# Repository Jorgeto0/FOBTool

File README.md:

# FOBtool Hardware

FOBtool Hardware is the KiCad source repository for the FOBtool handheld electronic platform. It contains the project-level schematic and PCB files, custom symbols and footprints, and supporting documentation used to develop and maintain the hardware design.

## Project contents

| Path | Purpose |
| --- | --- |
| `FOBtool_HW.kicad_pro` | Main KiCad project file. Open this file to work with the design. |
| `FOBtool_HW.kicad_sch` | Top-level hierarchical schematic. |
| `POWER.kicad_sch` | Battery, charging, power-path, monitoring, and regulated-supply circuitry. |
| `MAIN_CONTROLLER_sch.kicad_sch` | ESP32-S3 main-controller circuitry and system control interfaces. |
| `FOBtool_HW.kicad_pcb` | PCB layout file. |
| `Custom_Components/` | Project-specific symbol and footprint resources. |
| `docs/` | Short descriptions of the project and schematic sheets. |

## Opening the design

1. Install [KiCad](https://www.kicad.org/) 10.x or a compatible later version.
2. Clone or download the complete repository so the project files and custom libraries remain together.
3. Open `FOBtool_HW.kicad_pro` from KiCad's Project Manager.
4. Confirm that the project symbol and footprint libraries load without errors before editing the design.

Open the project file rather than an individual child sheet so KiCad retains the full hierarchy and project library configuration.

## Schematic documentation

See the [documentation index](docs/README.md) for the purpose of each schematic sheet currently included in the project.

## Repository use

This repository contains active engineering source files. Design files may change as schematic capture, verification, PCB layout, and manufacturing preparation progress. Manufacturing outputs should be issued separately as a controlled release.

## Confidentiality

This project contains proprietary client hardware information. Keep the repository private and share its contents only with authorized project participants.

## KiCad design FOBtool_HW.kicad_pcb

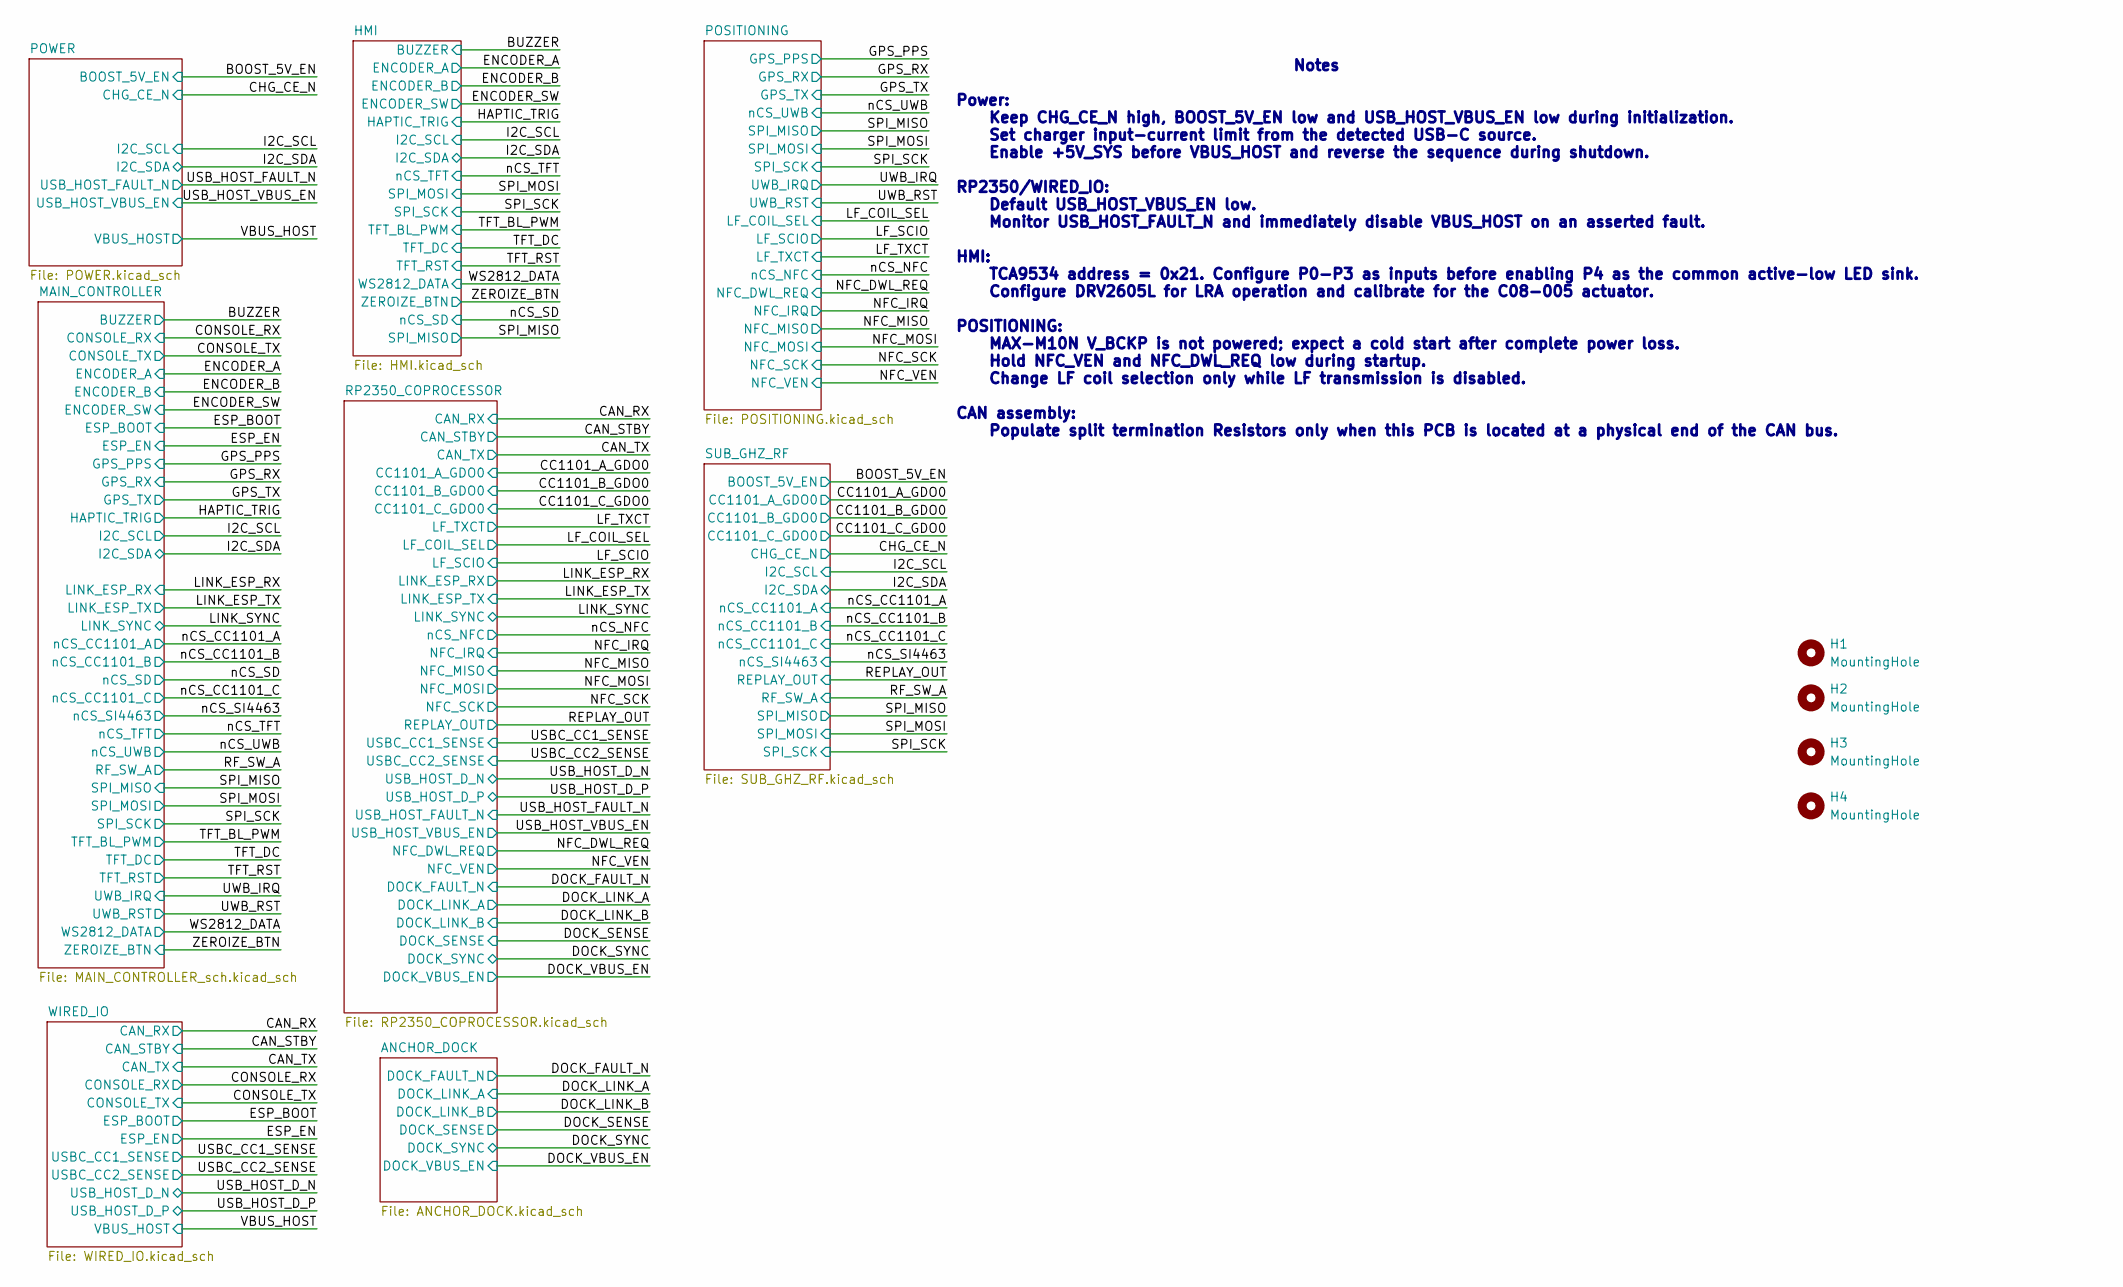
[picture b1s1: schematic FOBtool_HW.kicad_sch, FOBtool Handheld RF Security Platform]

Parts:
H1, H2, H3, H4: MountingHole; MountingHole_2.2mm_M2

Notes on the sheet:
Notes Power: Keep CHG_CE_N high, BOOST_5V_EN low and USB_HOST_VBUS_EN low during initialization. Set charger input-current limit from the detected USB-C source. Enable +5V_SYS before VBUS_HOST and reverse the sequence during shutdown. RP2350/WIRED_IO: Default USB_HOST_VBUS_EN low. Monitor USB_HOST_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

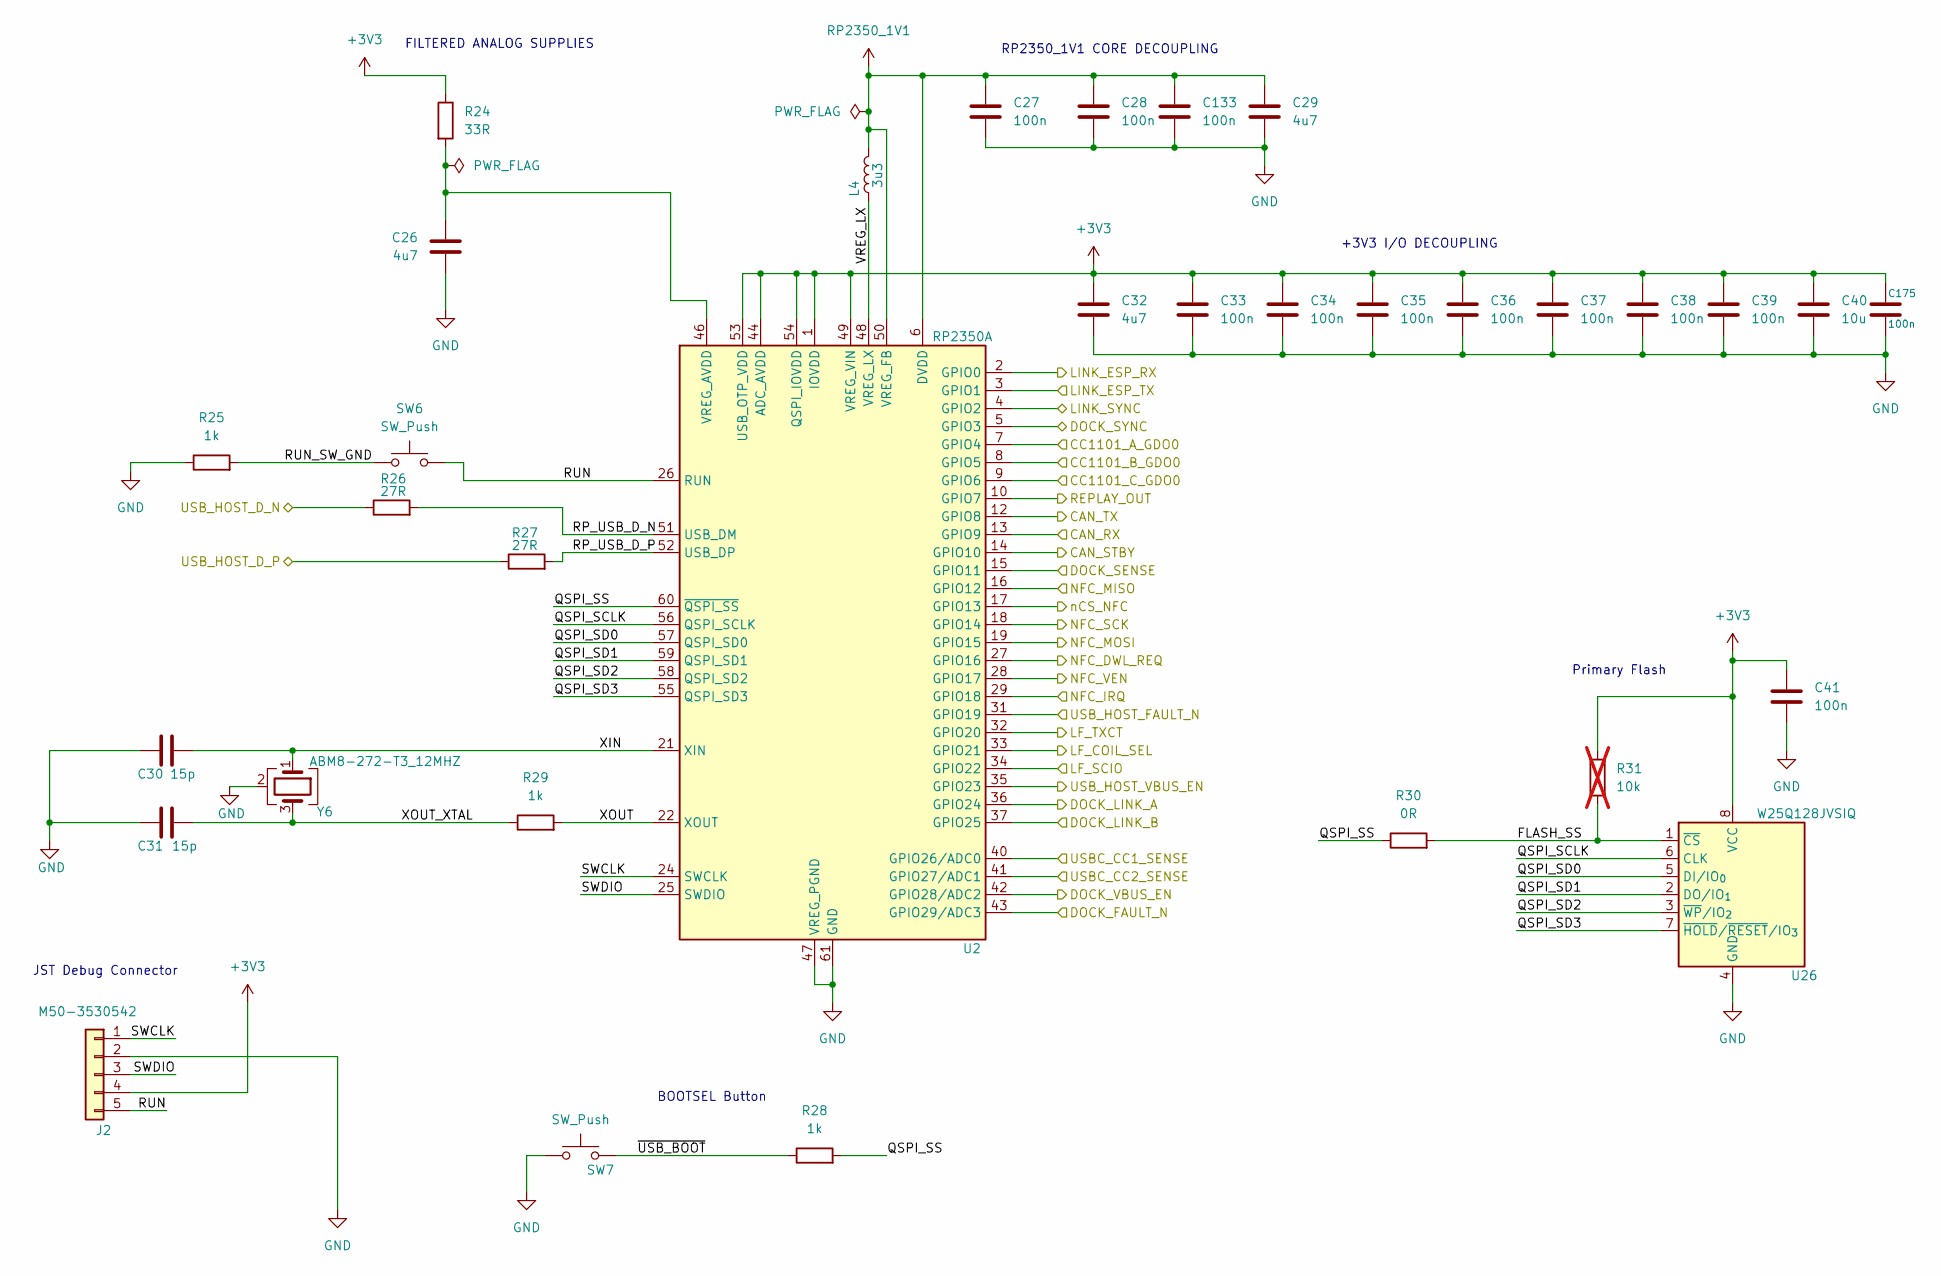
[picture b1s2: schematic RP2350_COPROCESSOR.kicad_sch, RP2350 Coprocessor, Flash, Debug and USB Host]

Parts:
C26, C29, C32: 4u7; C_0603_1608Metric; MPN GRM188Z71A475KE15D
C27, C28, C33, C34, C35, C36, C37, C38, C39, C41, C133, C175: 100n; C_0402_1005Metric; MPN GRM155R71C104KA88D
C30, C31: 15p; C_0402_1005Metric; MPN GJM1555C1H150JB01D
C40: 10u; C_0805_2012Metric; MPN GRM21BR71A106KE51L
J2: M50-3530542; PinHeader_1x05_P1.27mm_Vertical; MPN M50-3530542
L4: 3u3; L_Abracon_AOTA-B201610S_2.0x1.6mm; MPN AOTA-B201610S3R3-101-T
R24: 33R; R_0603_1608Metric; MPN RC0603FR-0733RL
R25, R28, R29: 1k; R_0603_1608Metric; MPN RC0603FR-071KL
R26, R27: 27R; R_0603_1608Metric; MPN RC0603FR-0727RL
R30: 0R; R_0603_1608Metric; MPN RC0603JR-070RL
R31: 10k; R_0603_1608Metric; MPN RC0603FR-0710KL; not fitted
SW6, SW7: SW_Push; SW_SPST_PTS810; MPN PTS810SJM250SMTR LFS
U2: RP2350A; QFN-60-1EP_7x7mm_P0.4mm_EP3.4x3.4mm; MPN SC1509(13)-A4
U26: W25Q128JVSIQ; SOIC-8_5.3x5.3mm_P1.27mm; MPN W25Q128JVSIQTR
Y6: ABM8-272-T3_12MHZ; Crystal_SMD_Abracon_ABM8G-4Pin_3.2x2.5mm; MPN ABM8-272-T3

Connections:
+3V3: C32.1, C33.1, C34.1, C35.1, C36.1, C37.1, C38.1, C39.1, C40.1, C41.1, C175.1, J2.4, R24.1, R31.1, U2.1 (IOVDD), U2.11 (IOVDD), U2.20 (IOVDD), U2.30 (IOVDD), U2.38 (IOVDD), U2.44 (ADC_AVDD), U2.45 (IOVDD), U2.49 (VREG_VIN), U2.53 (USB_OTP_VDD), U2.54 (QSPI_IOVDD), U26.8 (VCC); also elsewhere on the board
/CAN_RX: U2.13 (GPIO9); also elsewhere on the board
/CAN_STBY: U2.14 (GPIO10); also elsewhere on the board
/CAN_TX: U2.12 (GPIO8); also elsewhere on the board
/CC1101_A_GDO0: U2.7 (GPIO4); also elsewhere on the board
/CC1101_B_GDO0: U2.8 (GPIO5); also elsewhere on the board
/CC1101_C_GDO0: U2.9 (GPIO6); also elsewhere on the board
/DOCK_FAULT_N: U2.43 (GPIO29/ADC3); also elsewhere on the board
/DOCK_LINK_A: U2.36 (GPIO24); also elsewhere on the board
/DOCK_LINK_B: U2.37 (GPIO25); also elsewhere on the board
/DOCK_SENSE: U2.15 (GPIO11); also elsewhere on the board
/DOCK_SYNC: U2.5 (GPIO3); also elsewhere on the board
/DOCK_VBUS_EN: U2.42 (GPIO28/ADC2); also elsewhere on the board
/LF_COIL_SEL: U2.33 (GPIO21); also elsewhere on the board
/LF_SCIO: U2.34 (GPIO22); also elsewhere on the board
/LF_TXCT: U2.32 (GPIO20); also elsewhere on the board
/LINK_ESP_RX: U2.2 (GPIO0); also elsewhere on the board
/LINK_ESP_TX: U2.3 (GPIO1); also elsewhere on the board
/LINK_SYNC: U2.4 (GPIO2); also elsewhere on the board
/NFC_DWL_REQ: U2.27 (GPIO16); also elsewhere on the board
/NFC_IRQ: U2.29 (GPIO18); also elsewhere on the board
/NFC_MISO: U2.16 (GPIO12); also elsewhere on the board
/NFC_MOSI: U2.19 (GPIO15); also elsewhere on the board
/NFC_SCK: U2.18 (GPIO14); also elsewhere on the board
/NFC_VEN: U2.28 (GPIO17); also elsewhere on the board
/REPLAY_OUT: U2.10 (GPIO7); also elsewhere on the board
/RP2350_COPROCESSOR/FLASH_SS: R30.2, R31.2, U26.1 (~CS)
/RP2350_COPROCESSOR/QSPI_SCLK: U2.56 (QSPI_SCLK), U26.6 (CLK)
/RP2350_COPROCESSOR/QSPI_SD0: U2.57 (QSPI_SD0), U26.5 (DI/IO_{0})
/RP2350_COPROCESSOR/QSPI_SD1: U2.59 (QSPI_SD1), U26.2 (DO/IO_{1})
/RP2350_COPROCESSOR/QSPI_SD2: U2.58 (QSPI_SD2), U26.3 (~WP/IO_{2})
/RP2350_COPROCESSOR/QSPI_SD3: U2.55 (QSPI_SD3), U26.7 (~HOLD/~RESET/IO_{3})
/RP2350_COPROCESSOR/QSPI_SS: R28.2, R30.1, U2.60 (~QSPI_SS)
/RP2350_COPROCESSOR/RP_USB_D_N: R26.2, U2.51 (USB_DM)
/RP2350_COPROCESSOR/RP_USB_D_P: R27.2, U2.52 (USB_DP)
/RP2350_COPROCESSOR/RUN: J2.5, SW6.2, U2.26 (RUN)
/RP2350_COPROCESSOR/RUN_SW_GND: R25.2, SW6.1
/RP2350_COPROCESSOR/SWCLK: J2.1, U2.24 (SWCLK)
/RP2350_COPROCESSOR/SWDIO: J2.3, U2.25 (SWDIO)
/RP2350_COPROCESSOR/VREG_LX: L4.2, U2.48 (VREG_LX)
/RP2350_COPROCESSOR/XIN: C30.2, U2.21 (XIN), Y6.1
/RP2350_COPROCESSOR/XOUT: R29.2, U2.22 (XOUT)
/RP2350_COPROCESSOR/XOUT_XTAL: C31.2, R29.1, Y6.3
/RP2350_COPROCESSOR/~USB_BOOT: R28.1, SW7.2
/USBC_CC1_SENSE: U2.40 (GPIO26/ADC0); also elsewhere on the board
/USBC_CC2_SENSE: U2.41 (GPIO27/ADC1); also elsewhere on the board
/USB_HOST_D_N: R26.1; also elsewhere on the board
/USB_HOST_D_P: R27.1; also elsewhere on the board
/USB_HOST_FAULT_N: U2.31 (GPIO19); also elsewhere on the board
/USB_HOST_VBUS_EN: U2.35 (GPIO23); also elsewhere on the board
/nCS_NFC: U2.17 (GPIO13); also elsewhere on the board
GND: C26.2, C27.2, C28.2, C29.2, C30.1, C31.1, C32.2, C33.2, C34.2, C35.2, C36.2, C37.2, C38.2, C39.2, C40.2, C41.2, C133.2, C175.2, J2.2, R25.1, SW7.1, U2.47 (VREG_PGND), U2.61 (GND), U26.4 (GND), Y6.2 (G), Y6.4 (G); also elsewhere on the board
unnamed: C26.1, R24.2, U2.46 (VREG_AVDD)
RP2350_1V1: C27.1, C28.1, C29.1, C133.1, L4.1, U2.6 (DVDD), U2.23 (DVDD), U2.39 (DVDD), U2.50 (VREG_FB)

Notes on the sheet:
+3V3 I/O DECOUPLING
JST Debug Connector
RP2350_1V1 CORE DECOUPLING
Primary Flash
FILTERED ANALOG SUPPLIES
BOOTSEL Button

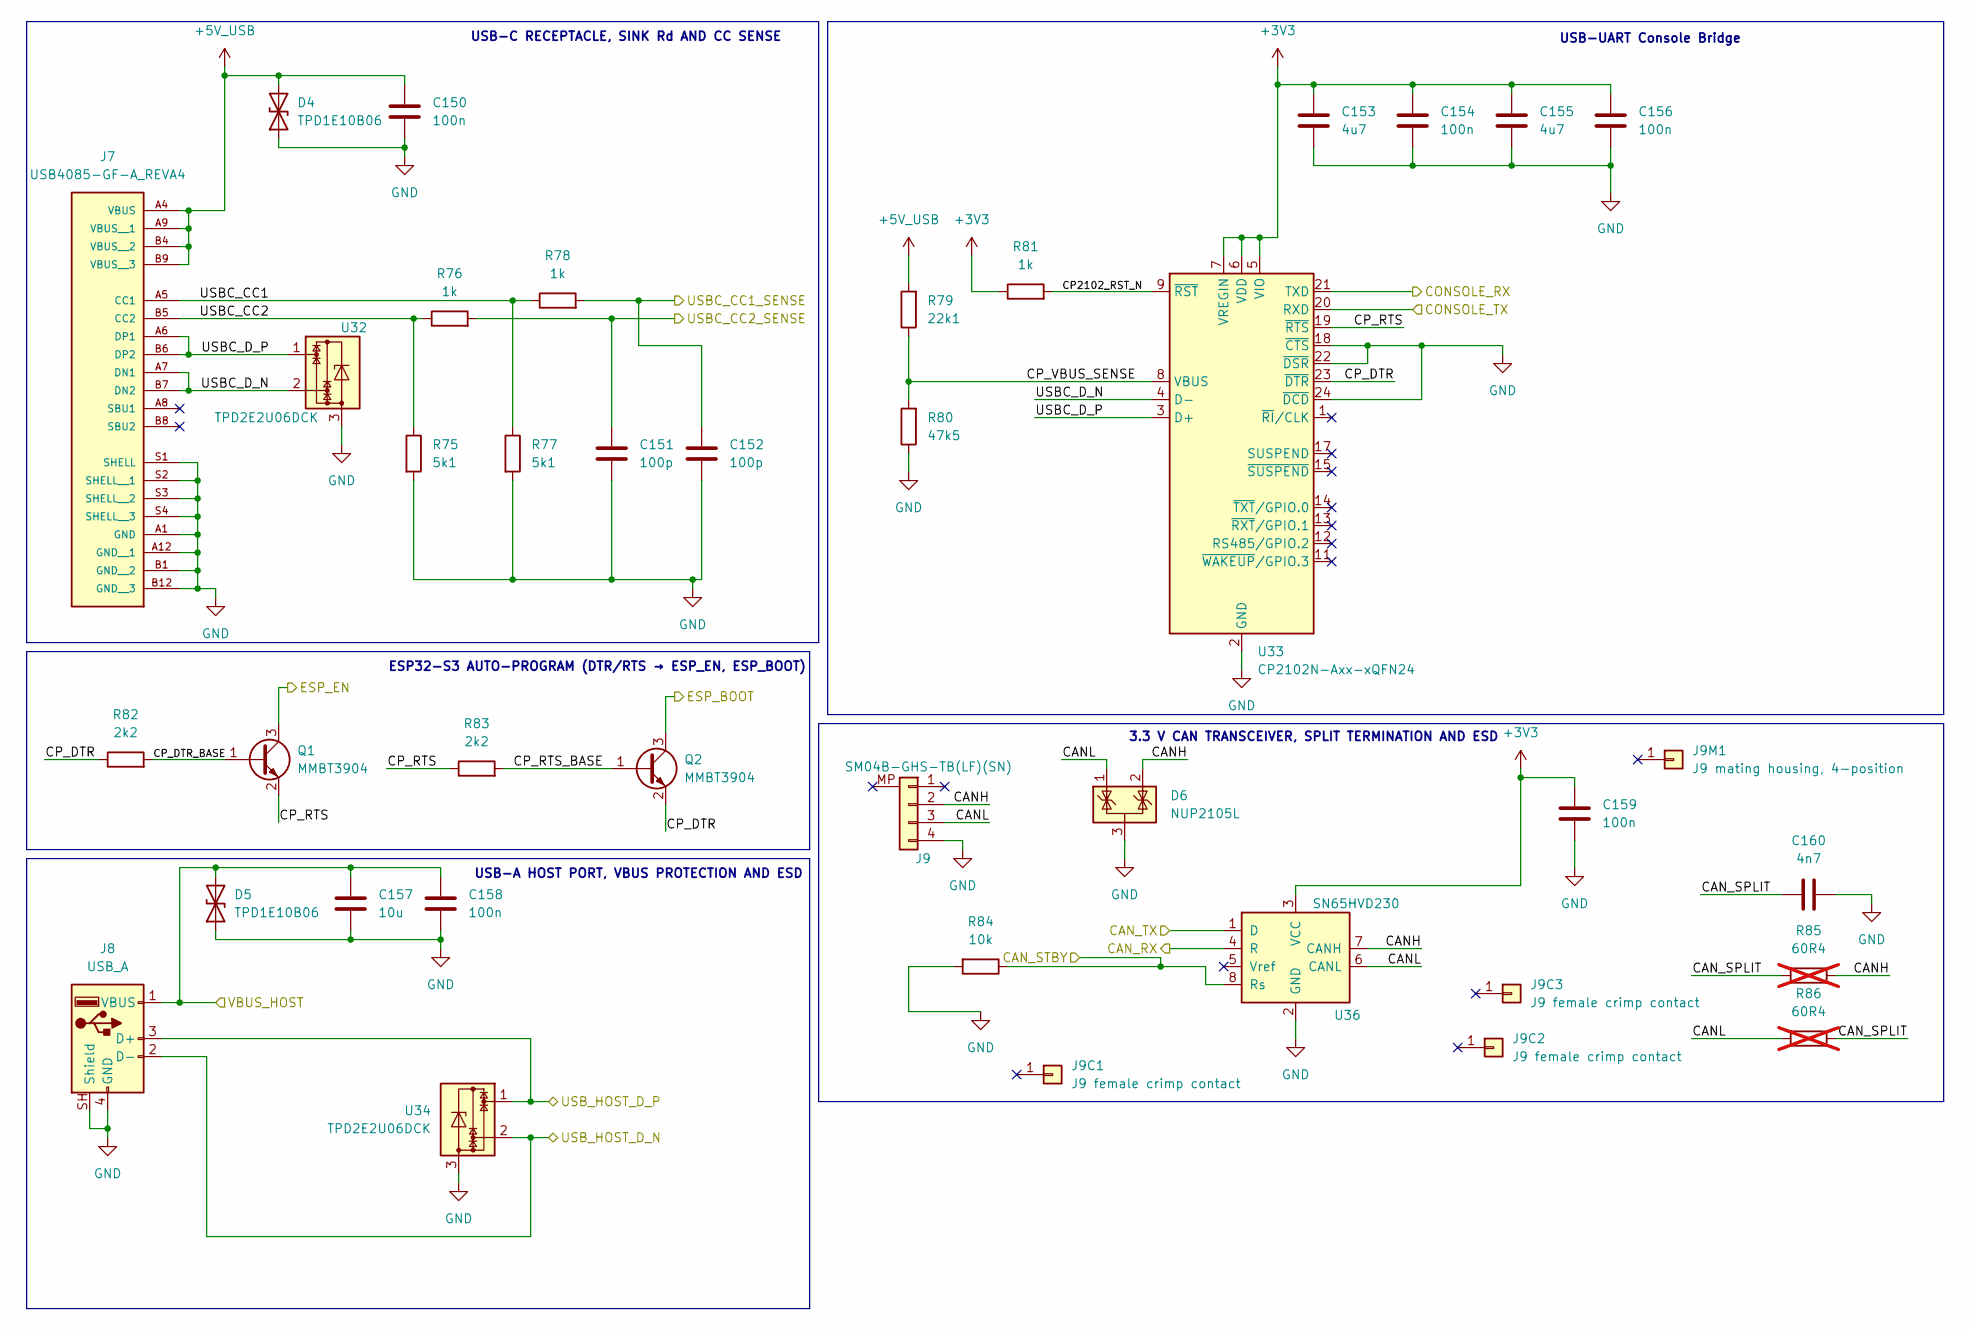
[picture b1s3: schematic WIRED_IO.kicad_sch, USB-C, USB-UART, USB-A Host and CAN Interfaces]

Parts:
C150, C154, C156, C158, C159: 100n; C_0603_1608Metric; MPN GRM188R71C104KA01D
C151, C152: 100p; C_0603_1608Metric; MPN GRM1885C1H101JA01D
C153, C155: 4u7; C_0603_1608Metric; MPN GRM188Z71A475KE15D
C157: 10u; C_0805_2012Metric; MPN GRM21BR71A106KE51L
C160: 4n7; C_0603_1608Metric; MPN GRM1885C1H472JA01D
D4, D5: TPD1E10B06; Texas_DPY0002A_0.6x1mm_P0.65mm; MPN TPD1E10B06DPYR
D6: NUP2105L; SOT-23; MPN NUP2105LT1G
J7: USB4085-GF-A_REVA4; GCT_USB4085-GF-A_REVA4; PARTREV A4
J8: USB_A; USB_A_Molex_67643_Horizontal; MPN 67643-3910
J9: SM04B-GHS-TB(LF)(SN); JST_GH_SM04B-GHS-TB_1x04-1MP_P1.25mm_Horizontal; MPN SM04B-GHS-TB(LF)(SN)
J9C1, J9C2, J9C3: J9 female crimp contact; MPN SSHL-002T-P0.2
J9M1: J9 mating housing, 4-position; MPN GHR-04V-S
Q1, Q2: MMBT3904; SOT-23; MPN MMBT3904LT1G
R75, R77: 5k1; R_0603_1608Metric; MPN RC0603FR-075K1L
R76, R78, R81: 1k; R_0603_1608Metric; MPN RC0603FR-071KL
R79: 22k1; R_0603_1608Metric; MPN RC0603FR-0722K1L
R80: 47k5; R_0603_1608Metric; MPN RC0603FR-0747K5L
R82, R83: 2k2; R_0603_1608Metric; MPN RC0603FR-072K2L
R84: 10k; R_0603_1608Metric; MPN RC0603FR-0710KL
R85, R86: 60R4; R_0603_1608Metric; MPN RC0603FR-0760R4L; not fitted
U32, U34: TPD2E2U06DCK; SOT-323_SC-70; MPN TPD2E2U06DCKR
U33: CP2102N-Axx-xQFN24; QFN-24-1EP_4x4mm_P0.5mm_EP2.6x2.6mm; MPN CP2102N-A02-GQFN24R
U36: SN65HVD230; SOIC-8_3.9x4.9mm_P1.27mm; MPN SN65HVD230DR

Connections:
+3V3: C153.1, C154.1, C155.1, C156.1, C159.2, R81.1, U33.5 (VIO), U33.6 (VDD), U33.7 (VREGIN), U36.3 (VCC); also elsewhere on the board
+5V_USB: C150.1, D4.2 (A2), J7.A4 (VBUS), J7.A9 (VBUS__1), J7.B4 (VBUS__2), J7.B9 (VBUS__3), R79.2; also elsewhere on the board
/CAN_RX: U36.4 (R); also elsewhere on the board
/CAN_STBY: R84.1, U36.8 (Rs); also elsewhere on the board
/CAN_TX: U36.1 (D); also elsewhere on the board
/CONSOLE_RX: U33.21 (TXD); also elsewhere on the board
/CONSOLE_TX: U33.20 (RXD); also elsewhere on the board
/ESP_BOOT: Q2.3 (C); also elsewhere on the board
/ESP_EN: Q1.3 (C); also elsewhere on the board
/USBC_CC1_SENSE: C152.1, R78.2; also elsewhere on the board
/USBC_CC2_SENSE: C151.1, R76.2; also elsewhere on the board
/USB_HOST_D_N: J8.2 (D-), U34.2; also elsewhere on the board
/USB_HOST_D_P: J8.3 (D+), U34.1; also elsewhere on the board
/VBUS_HOST: C157.1, C158.1, D5.2 (A2), J8.1 (VBUS); also elsewhere on the board
/WIRED_IO/CANH: D6.2 (K), J9.2, R85.1, U36.7 (CANH)
/WIRED_IO/CANL: D6.1 (K), J9.3, R86.2, U36.6 (CANL)
/WIRED_IO/CAN_SPLIT: C160.2, R85.2, R86.1
/WIRED_IO/CP2102_RST_N: R81.2, U33.9 (~RST)
/WIRED_IO/CP_DTR: Q2.2 (E), R82.1, U33.23 (~DTR)
/WIRED_IO/CP_DTR_BASE: Q1.1 (B), R82.2
/WIRED_IO/CP_RTS: Q1.2 (E), R83.1, U33.19 (~RTS)
/WIRED_IO/CP_RTS_BASE: Q2.1 (B), R83.2
/WIRED_IO/CP_VBUS_SENSE: R79.1, R80.2, U33.8 (VBUS)
/WIRED_IO/USBC_CC1: J7.A5 (CC1), R77.1, R78.1
/WIRED_IO/USBC_CC2: J7.B5 (CC2), R75.1, R76.1
/WIRED_IO/USBC_D_N: J7.A7 (DN1), J7.B7 (DN2), U32.2, U33.4 (D-)
/WIRED_IO/USBC_D_P: J7.A6 (DP1), J7.B6 (DP2), U32.1, U33.3 (D+)
GND: C150.2, C151.2, C152.2, C153.2, C154.2, C155.2, C156.2, C157.2, C158.2, C159.1, C160.1, D4.1 (A1), D5.1 (A1), D6.3 (A), J7.A1 (GND), J7.A12 (GND__1), J7.B1 (GND__2), J7.B12 (GND__3), J7.S1 (SHELL), J7.S2 (SHELL__1), J7.S3 (SHELL__2), J7.S4 (SHELL__3), J8.4 (GND), J8.SH (Shield), J9.4, R75.2, R77.2, R80.1, R84.2, U32.3, U33.2 (GND), U33.18 (~CTS), U33.22 (~DSR), U33.24 (~DCD), U33.25 (GND), U34.3, U36.2 (GND); also elsewhere on the board

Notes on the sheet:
ESP32-S3 AUTO-PROGRAM (DTR/RTS → ESP_EN, ESP_BOOT)
USB-C RECEPTACLE, SINK Rd AND CC SENSE
3.3 V CAN TRANSCEIVER, SPLIT TERMINATION AND ESD
USB-A HOST PORT, VBUS PROTECTION AND ESD
USB-UART Console Bridge

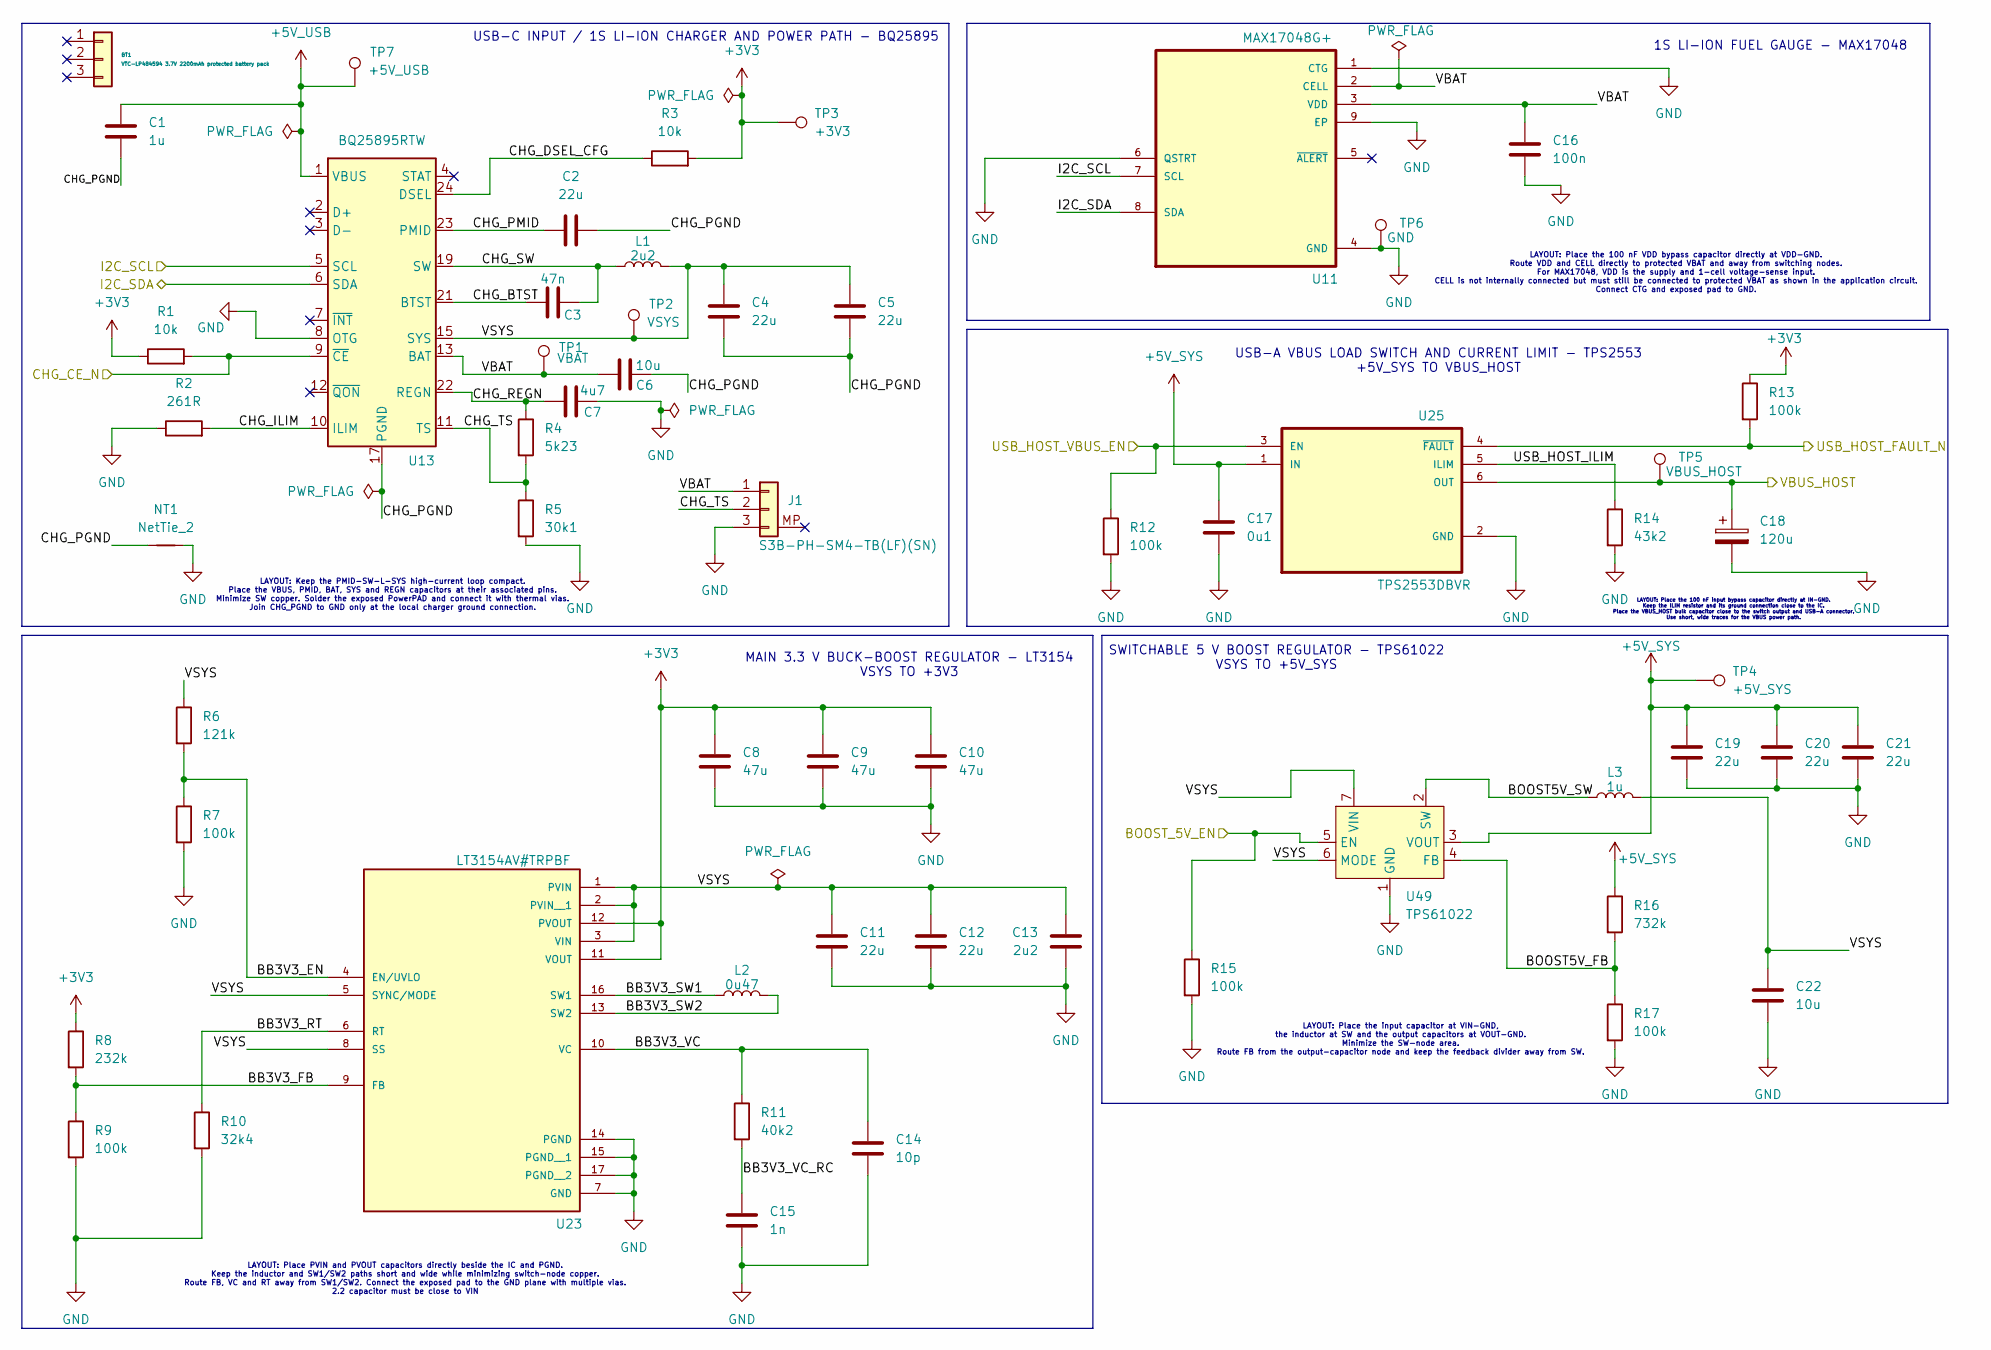
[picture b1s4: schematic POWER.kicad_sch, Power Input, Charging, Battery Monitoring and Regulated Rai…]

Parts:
BT1: VTC-LP484594 3.7V 2200mAh protected battery pack; MPN VTC-LP484594
C1: 1u; C_0603_1608Metric; MPN GRM188R71C105KA12D
C2, C4, C5, C11, C12, C19, C20, C21: 22u; C_1206_3216Metric; MPN GRM31CR71A226KE15L
C3: 47n; C_0603_1608Metric; MPN GRM188R71C473KA01D
C6, C22: 10u; C_0805_2012Metric; MPN GRM21BR71A106KE51L
C7: 4u7; C_0805_2012Metric; MPN GRM21BR71A475KA73L
C8, C9, C10: 47u; C_1210_3225Metric; MPN GRM32ER71A476KE15L
C13: 2u2; C_0603_1608Metric; MPN GRM188R71A225KE15D
C14: 10p; C_0603_1608Metric; MPN GRM1885C1H100JA01D
C15: 1n; C_0603_1608Metric; MPN GRM1885C1H102JA01D
C16: 100n; C_0603_1608Metric; MPN GRM188R71C104KA01D
C17: 0u1; C_0603_1608Metric; MPN GRM188R71C104KA01D
C18: 120u; CP_Panasonic_EEF-TX_7.3x4.3mm; MPN EEF-TX0J121RF
J1: S3B-PH-SM4-TB(LF)(SN); JST_PH_S3B-PH-SM4-TB_1x03-1MP_P2.00mm_Horizontal; MPN S3B-PH-SM4-TB(LF)(SN)
L1: 2u2; L_Wuerth_MAPI-4020; MPN 74438356022
L2: 0u47; L_Wuerth_MAPI-4020; MPN 744383560047HT
L3: 1u; L_Wuerth_HCI-5040; MPN 744316100
NT1: NetTie_2; NetTie_2_SMD_3.0mm_Current; MPN N/A
R1, R3: 10k; R_0603_1608Metric; MPN RC0603FR-0710KL
R2: 261R; R_0603_1608Metric; MPN AF0603FR-07261RL
R4: 5k23; R_0603_1608Metric; MPN RC0603FR-075K23L
R5: 30k1; R_0603_1608Metric; MPN RC0603FR-0730K1L
R6: 121k; R_0603_1608Metric; MPN RC0603FR-07121KL
R7, R9, R12, R13, R15, R17: 100k; R_0603_1608Metric; MPN RC0603FR-07100KL
R8: 232k; R_0603_1608Metric; MPN RC0603FR-07232KL
R10: 32k4; R_0603_1608Metric; MPN RC0603FR-0732K4L
R11: 40k2; R_0603_1608Metric; MPN RC0603FR-0740K2L
R14: 43k2; R_0603_1608Metric; MPN RC0603FR-0743K2L
R16: 732k; R_0603_1608Metric; MPN RC0603FR-07732KL
TP1: VBAT; TestPoint_Pad_D1.5mm; MPN N/A
TP2: VSYS; TestPoint_Pad_D1.5mm; MPN N/A
TP3: +3V3; TestPoint_Pad_D1.5mm; MPN N/A
TP4: +5V_SYS; TestPoint_Pad_D1.5mm; MPN N/A
TP5: VBUS_HOST; TestPoint_Pad_D1.5mm; MPN N/A
TP6: GND; TestPoint_Pad_D1.5mm; MPN N/A
TP7: +5V_USB; TestPoint_Pad_D1.5mm; MPN N/A
U11: MAX17048G+; SON50P200X200X80-9N; MPN MAX17048G+T10
U13: BQ25895RTW; Texas_RTW_WQFN-24-1EP_4x4mm_P0.5mm_EP2.7x2.7mm_ThermalVias; MPN BQ25895RTWR
U23: LT3154AV#TRPBF; QFN50P300X300X83-17N; PARTREV A
U25: TPS2553DBVR; SOT95P280X145-6N; MPN TPS2553DBVR
U49: TPS61022; Texas_RWU0007A_VQFN-7_2x2mm_P0.5mm; MPN TPS61022RWUR

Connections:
+3V3: C8.1, C9.1, C10.1, R1.1, R3.2, R8.1, R13.1, TP3.1 (1_1), U23.11 (VOUT), U23.12 (PVOUT); also elsewhere on the board
+5V_SYS: C17.2, C19.2, C20.2, C21.2, R16.1, TP4.1 (1_1), U25.1 (IN), U49.3 (VOUT); also elsewhere on the board
+5V_USB: C1.2, TP7.1 (1_1), U13.1 (VBUS); also elsewhere on the board
/BOOST_5V_EN: R15.1, U49.5 (EN); also elsewhere on the board
/CHG_CE_N: R1.2, U13.9 (~CE); also elsewhere on the board
/I2C_SCL: U11.7 (SCL), U13.5 (SCL); also elsewhere on the board
/I2C_SDA: U11.8 (SDA), U13.6 (SDA); also elsewhere on the board
/POWER/BB3V3_EN: R6.2, R7.1, U23.4 (EN/UVLO)
/POWER/BB3V3_FB: R8.2, R9.1, U23.9 (FB)
/POWER/BB3V3_RT: R10.1, U23.6 (RT)
/POWER/BB3V3_SW1: L2.1, U23.16 (SW1)
/POWER/BB3V3_SW2: L2.2, U23.13 (SW2)
/POWER/BB3V3_VC: C14.2, R11.1, U23.10 (VC)
/POWER/BB3V3_VC_RC: C15.2, R11.2
/POWER/BOOST5V_FB: R16.2, R17.1, U49.4 (FB)
/POWER/BOOST5V_SW: L3.1, U49.2 (SW)
/POWER/CHG_BTST: C3.1, U13.21 (BTST)
/POWER/CHG_DSEL_CFG: R3.1, U13.24 (DSEL)
/POWER/CHG_ILIM: R2.2, U13.10 (ILIM)
/POWER/CHG_PGND: C1.1, C2.2, C4.2, C5.2, C6.2, NT1.2, U13.17 (PGND), U13.18 (PGND), U13.25 (PGND)
/POWER/CHG_PMID: C2.1, U13.23 (PMID)
/POWER/CHG_REGN: C7.1, R4.1, U13.22 (REGN)
/POWER/CHG_SW: C3.2, L1.1, U13.19 (SW), U13.20 (SW)
/POWER/CHG_TS: J1.2, R4.2, R5.1, U13.11 (TS)
/POWER/USB_HOST_ILIM: R14.1, U25.5 (ILIM)
/POWER/VBAT: C6.1, C16.1, J1.1, TP1.1 (1_1), U11.2 (CELL), U11.3 (VDD), U13.13 (BAT), U13.14 (BAT)
/POWER/VSYS: C4.1, C5.1, C11.1, C12.1, C13.1, C22.2, L1.2, L3.2, R6.1, TP2.1 (1_1), U13.15 (SYS), U13.16 (SYS), U23.1 (PVIN), U23.2 (PVIN__1), U23.3 (VIN), U23.5 (SYNC/MODE), U23.8 (SS), U49.6 (MODE), U49.7 (VIN)
/USB_HOST_FAULT_N: R13.2, U25.4 (~FAULT); also elsewhere on the board
/USB_HOST_VBUS_EN: R12.1, U25.3 (EN); also elsewhere on the board
/VBUS_HOST: C18.1, TP5.1 (1_1), U25.6 (OUT); also elsewhere on the board
GND: C7.2, C8.2, C9.2, C10.2, C11.2, C12.2, C13.2, C14.1, C15.1, C16.2, C17.1, C18.2, C19.1, C20.1, C21.1, C22.1, J1.3, NT1.1, R2.1, R5.2, R7.2, R9.2, R10.2, R12.2, R14.2, R15.2, R17.2, TP6.1 (1_1), U11.1 (CTG), U11.4 (GND), U11.6 (QSTRT), U11.9 (EP), U13.8 (OTG), U23.7 (GND), U23.14 (PGND), U23.15 (PGND__1), U23.17 (PGND__2), U25.2 (GND), U49.1 (GND); also elsewhere on the board

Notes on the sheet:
LAYOUT: Place the 100 nF input bypass capacitor directly at IN-GND. Keep the ILIM resistor and its ground connection close to the IC. Place the VBUS_HOST bulk capacitor close to the switch output and USB-A connector. Use short, wide traces for the VBUS power path.
LAYOUT: Keep the PMID-SW-L-SYS high-current loop compact. Place the VBUS, PMID, BAT, SYS and REGN capacitors at their associated pins. Minimize SW copper. Solder the exposed PowerPAD and connect it with thermal vias. Join CHG_PGND to GND only at the local charger ground connection.
SWITCHABLE 5 V BOOST REGULATOR - TPS61022 VSYS TO +5V_SYS
1S LI-ION FUEL GAUGE - MAX17048
LAYOUT: Place the 100 nF VDD bypass capacitor directly at VDD-GND. Route VDD and CELL directly to protected VBAT and away from switching nodes. For MAX17048, VDD is the supply and 1-cell voltage-sense input. CELL is not internally connected but must still be connected to protected VBAT as shown in 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
USB-C INPUT / 1S LI-ION CHARGER AND POWER PATH - BQ25895
MAIN 3.3 V BUCK-BOOST REGULATOR - LT3154 VSYS TO +3V3
LAYOUT: Place PVIN and PVOUT capacitors directly beside the IC and PGND. Keep the inductor and SW1/SW2 paths short and wide while minimizing switch-node copper. Route FB, VC and RT away from SW1/SW2. Connect the exposed pad to the GND plane with multiple vias. 2.2 capacitor must be close to VIN
USB-A VBUS LOAD SWITCH AND CURRENT LIMIT - TPS2553 +5V_SYS TO VBUS_HOST
LAYOUT: Place the input capacitor at VIN-GND, the inductor at SW and the output capacitors at VOUT-GND. Minimize the SW-node area. Route FB from the output-capacitor node and keep the feedback divider away from SW.
